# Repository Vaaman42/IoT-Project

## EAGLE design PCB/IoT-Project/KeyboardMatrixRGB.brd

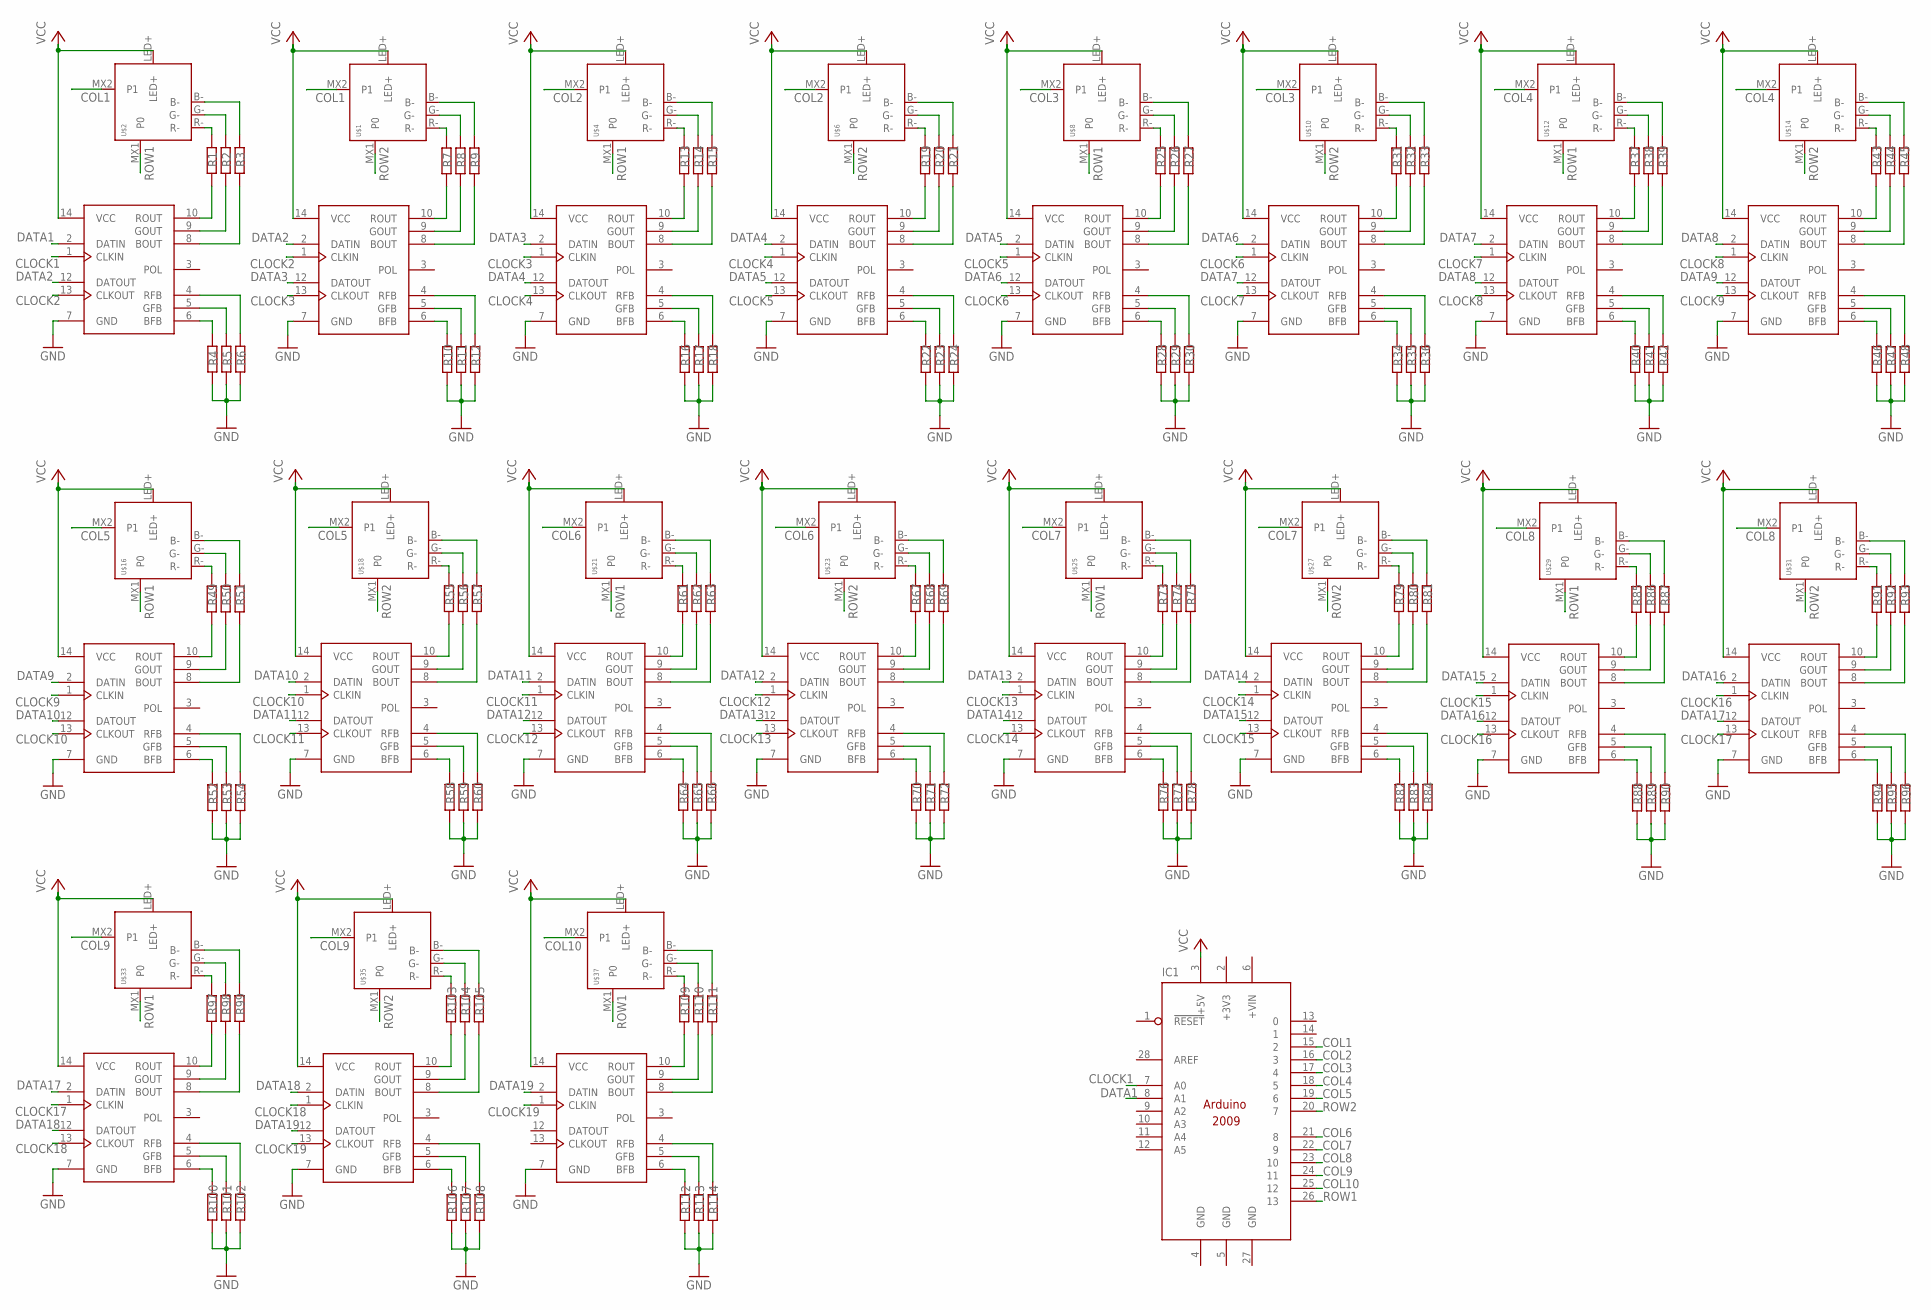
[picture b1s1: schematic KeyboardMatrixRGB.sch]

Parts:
IC1: ARDUINO2009_10; ARDUINO2009
R1, R2, R3, R4, R5, R6, R7, R8, R9, R10, R11, R12, R13, R14, R15, R16, R17, R18, R19, R20, R21, R22, R23, R24, R25, R26, R27, R28, R29, R30, R31, R32, R33, R34, R35, R36, R37, R38, R39, R40, R41, R42, R43, R44, R45, R46, R47, R48, R49, R50, R51, R52, R53, R54, R55, R56, R57, R58, R59, R60, R61, R62, R63, R64, R65, R66, R67, R68, R69, R70, R71, R72, R73, R74, R75, R76, R77, R78, R79, R80, R81, R82, R83, R84, R85, R86, R87, R88, R89, R90, R91, R92, R93, R94, R95, R96, R97, R98, R99, R100, R101, R102, R103, R104, R105, R106, R107, R108, R109, R110, R111, R112, R113, R114: R-EU_0204/5; 0204/5
U$1, U$2, U$4, U$6, U$8, U$10, U$12, U$14, U$16, U$18, U$21, U$23, U$25, U$27, U$29, U$31, U$33, U$35, U$37: KEYSWITCH-RGBLED-MX-1U-RGB; MX-1U-RGB
U$3, U$5, U$7, U$9, U$11, U$13, U$15, U$17, U$19, U$20, U$22, U$24, U$26, U$28, U$30, U$32, U$34, U$36, U$38: WS2801; SOP14

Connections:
+3V3: IC1.2 (+3V3)
CLOCK1: IC1.7 (A0), U$20.1 (CLKIN)
CLOCK2: U$3.1 (CLKIN), U$20.13 (CLKOUT)
CLOCK3: U$3.13 (CLKOUT), U$5.1 (CLKIN)
CLOCK4: U$5.13 (CLKOUT), U$7.1 (CLKIN)
CLOCK5: U$7.13 (CLKOUT), U$9.1 (CLKIN)
CLOCK6: U$9.13 (CLKOUT), U$11.1 (CLKIN)
CLOCK7: U$11.13 (CLKOUT), U$13.1 (CLKIN)
CLOCK8: U$13.13 (CLKOUT), U$15.1 (CLKIN)
CLOCK9: U$15.13 (CLKOUT), U$17.1 (CLKIN)
CLOCK10: U$17.13 (CLKOUT), U$19.1 (CLKIN)
CLOCK11: U$19.13 (CLKOUT), U$22.1 (CLKIN)
CLOCK12: U$22.13 (CLKOUT), U$24.1 (CLKIN)
CLOCK13: U$24.13 (CLKOUT), U$26.1 (CLKIN)
CLOCK14: U$26.13 (CLKOUT), U$28.1 (CLKIN)
CLOCK15: U$28.13 (CLKOUT), U$30.1 (CLKIN)
CLOCK16: U$30.13 (CLKOUT), U$32.1 (CLKIN)
CLOCK17: U$32.13 (CLKOUT), U$34.1 (CLKIN)
CLOCK18: U$34.13 (CLKOUT), U$36.1 (CLKIN)
CLOCK19: U$36.13 (CLKOUT), U$38.1 (CLKIN)
COL1: IC1.15 (2), U$1.MX2 (P1), U$2.MX2 (P1)
COL2: IC1.16 (3), U$4.MX2 (P1), U$6.MX2 (P1)
COL3: IC1.17 (4), U$8.MX2 (P1), U$10.MX2 (P1)
COL4: IC1.18 (5), U$12.MX2 (P1), U$14.MX2 (P1)
COL5: IC1.19 (6), U$16.MX2 (P1), U$18.MX2 (P1)
COL6: IC1.21 (8), U$21.MX2 (P1), U$23.MX2 (P1)
COL7: IC1.22 (9), U$25.MX2 (P1), U$27.MX2 (P1)
COL8: IC1.23 (10), U$29.MX2 (P1), U$31.MX2 (P1)
COL9: IC1.24 (11), U$33.MX2 (P1), U$35.MX2 (P1)
COL10: IC1.25 (12), U$37.MX2 (P1)
DATA1: IC1.8 (A1), U$20.2 (DATIN)
DATA2: U$3.2 (DATIN), U$20.12 (DATOUT)
DATA3: U$3.12 (DATOUT), U$5.2 (DATIN)
DATA4: U$5.12 (DATOUT), U$7.2 (DATIN)
DATA5: U$7.12 (DATOUT), U$9.2 (DATIN)
DATA6: U$9.12 (DATOUT), U$11.2 (DATIN)
DATA7: U$11.12 (DATOUT), U$13.2 (DATIN)
DATA8: U$13.12 (DATOUT), U$15.2 (DATIN)
DATA9: U$15.12 (DATOUT), U$17.2 (DATIN)
DATA10: U$17.12 (DATOUT), U$19.2 (DATIN)
DATA11: U$19.12 (DATOUT), U$22.2 (DATIN)
DATA12: U$22.12 (DATOUT), U$24.2 (DATIN)
DATA13: U$24.12 (DATOUT), U$26.2 (DATIN)
DATA14: U$26.12 (DATOUT), U$28.2 (DATIN)
DATA15: U$28.12 (DATOUT), U$30.2 (DATIN)
DATA16: U$30.12 (DATOUT), U$32.2 (DATIN)
DATA17: U$32.12 (DATOUT), U$34.2 (DATIN)
DATA18: U$34.12 (DATOUT), U$36.2 (DATIN)
DATA19: U$36.12 (DATOUT), U$38.2 (DATIN)
GND: IC1.4 (GND), IC1.5 (GND), IC1.27 (GND), R4.1, R5.1, R6.1, R10.1, R11.1, R12.1, R16.1, R17.1, R18.1, R22.1, R23.1, R24.1, R28.1, R29.1, R30.1, R34.1, R35.1, R36.1, R40.1, R41.1, R42.1, R46.1, R47.1, R48.1, R52.1, R53.1, R54.1, R58.1, R59.1, R60.1, R64.1, R65.1, R66.1, R70.1, R71.1, R72.1, R76.1, R77.1, R78.1, R82.1, R83.1, R84.1, R88.1, R89.1, R90.1, R94.1, R95.1, R96.1, R100.1, R101.1, R102.1, R106.1, R107.1, R108.1, R112.1, R113.1, R114.1, U$3.7 (GND), U$5.7 (GND), U$7.7 (GND), U$9.7 (GND), U$11.7 (GND), U$13.7 (GND), U$15.7 (GND), U$17.7 (GND), U$19.7 (GND), U$20.7 (GND), U$22.7 (GND), U$24.7 (GND), U$26.7 (GND), U$28.7 (GND), U$30.7 (GND), U$32.7 (GND), U$34.7 (GND), U$36.7 (GND), U$38.7 (GND)
unnamed: R1.2, U$2.R-
unnamed: R2.2, U$2.G-
unnamed: R3.2, U$2.B-
unnamed: R1.1, U$20.10 (ROUT)
unnamed: R2.1, U$20.9 (GOUT)
unnamed: R3.1, U$20.8 (BOUT)
unnamed: R4.2, U$20.6 (BFB)
unnamed: R5.2, U$20.5 (GFB)
unnamed: R6.2, U$20.4 (RFB)
unnamed: R49.2, U$16.R-
unnamed: R7.2, U$1.R-
unnamed: R8.2, U$1.G-
unnamed: R9.2, U$1.B-
unnamed: R7.1, U$3.10 (ROUT)
unnamed: R8.1, U$3.9 (GOUT)
unnamed: R9.1, U$3.8 (BOUT)
unnamed: R10.2, U$3.6 (BFB)
unnamed: R11.2, U$3.5 (GFB)
unnamed: R12.2, U$3.4 (RFB)
unnamed: R13.2, U$4.R-
unnamed: R14.2, U$4.G-
unnamed: R15.2, U$4.B-
unnamed: R13.1, U$5.10 (ROUT)
unnamed: R14.1, U$5.9 (GOUT)
unnamed: R15.1, U$5.8 (BOUT)
unnamed: R16.2, U$5.6 (BFB)
unnamed: R17.2, U$5.5 (GFB)
unnamed: R18.2, U$5.4 (RFB)
unnamed: R19.2, U$6.R-
unnamed: R20.2, U$6.G-
unnamed: R21.2, U$6.B-
unnamed: R19.1, U$7.10 (ROUT)
unnamed: R20.1, U$7.9 (GOUT)
unnamed: R21.1, U$7.8 (BOUT)
unnamed: R22.2, U$7.6 (BFB)
unnamed: R23.2, U$7.5 (GFB)
unnamed: R24.2, U$7.4 (RFB)
unnamed: R25.2, U$8.R-
unnamed: R26.2, U$8.G-
unnamed: R27.2, U$8.B-
unnamed: R25.1, U$9.10 (ROUT)
unnamed: R26.1, U$9.9 (GOUT)
unnamed: R27.1, U$9.8 (BOUT)
unnamed: R28.2, U$9.6 (BFB)
unnamed: R29.2, U$9.5 (GFB)
unnamed: R30.2, U$9.4 (RFB)
unnamed: R31.2, U$10.R-
unnamed: R32.2, U$10.G-
unnamed: R33.2, U$10.B-
unnamed: R31.1, U$11.10 (ROUT)
unnamed: R32.1, U$11.9 (GOUT)
unnamed: R33.1, U$11.8 (BOUT)
unnamed: R34.2, U$11.6 (BFB)
unnamed: R35.2, U$11.5 (GFB)
unnamed: R36.2, U$11.4 (RFB)
unnamed: R37.2, U$12.R-
unnamed: R38.2, U$12.G-
unnamed: R39.2, U$12.B-
unnamed: R37.1, U$13.10 (ROUT)
unnamed: R38.1, U$13.9 (GOUT)
unnamed: R39.1, U$13.8 (BOUT)
unnamed: R40.2, U$13.6 (BFB)
unnamed: R41.2, U$13.5 (GFB)
unnamed: R42.2, U$13.4 (RFB)
unnamed: R43.2, U$14.R-
unnamed: R44.2, U$14.G-
unnamed: R45.2, U$14.B-
unnamed: R43.1, U$15.10 (ROUT)
unnamed: R44.1, U$15.9 (GOUT)
unnamed: R45.1, U$15.8 (BOUT)
unnamed: R46.2, U$15.6 (BFB)
unnamed: R47.2, U$15.5 (GFB)
unnamed: R48.2, U$15.4 (RFB)
unnamed: R50.2, U$16.G-
unnamed: R51.2, U$16.B-
unnamed: R49.1, U$17.10 (ROUT)
unnamed: R50.1, U$17.9 (GOUT)
unnamed: R51.1, U$17.8 (BOUT)
unnamed: R52.2, U$17.6 (BFB)
unnamed: R53.2, U$17.5 (GFB)
unnamed: R54.2, U$17.4 (RFB)
unnamed: R97.2, U$33.R-
unnamed: R55.2, U$18.R-
unnamed: R56.2, U$18.G-
unnamed: R57.2, U$18.B-
unnamed: R55.1, U$19.10 (ROUT)
unnamed: R56.1, U$19.9 (GOUT)
unnamed: R57.1, U$19.8 (BOUT)
unnamed: R58.2, U$19.6 (BFB)
unnamed: R59.2, U$19.5 (GFB)
unnamed: R60.2, U$19.4 (RFB)
unnamed: R61.2, U$21.R-
unnamed: R62.2, U$21.G-
unnamed: R63.2, U$21.B-
unnamed: R61.1, U$22.10 (ROUT)
unnamed: R62.1, U$22.9 (GOUT)
unnamed: R63.1, U$22.8 (BOUT)
unnamed: R64.2, U$22.6 (BFB)
unnamed: R65.2, U$22.5 (GFB)
unnamed: R66.2, U$22.4 (RFB)
unnamed: R67.2, U$23.R-
unnamed: R68.2, U$23.G-
unnamed: R69.2, U$23.B-
unnamed: R67.1, U$24.10 (ROUT)
unnamed: R68.1, U$24.9 (GOUT)
unnamed: R69.1, U$24.8 (BOUT)
unnamed: R70.2, U$24.6 (BFB)
unnamed: R71.2, U$24.5 (GFB)
unnamed: R72.2, U$24.4 (RFB)
unnamed: R73.2, U$25.R-
unnamed: R74.2, U$25.G-
unnamed: R75.2, U$25.B-
unnamed: R73.1, U$26.10 (ROUT)
unnamed: R74.1, U$26.9 (GOUT)
unnamed: R75.1, U$26.8 (BOUT)
unnamed: R76.2, U$26.6 (BFB)
unnamed: R77.2, U$26.5 (GFB)
unnamed: R78.2, U$26.4 (RFB)
unnamed: R79.2, U$27.R-
unnamed: R80.2, U$27.G-
unnamed: R81.2, U$27.B-
unnamed: R79.1, U$28.10 (ROUT)
unnamed: R80.1, U$28.9 (GOUT)
unnamed: R81.1, U$28.8 (BOUT)
unnamed: R82.2, U$28.6 (BFB)
unnamed: R83.2, U$28.5 (GFB)
unnamed: R84.2, U$28.4 (RFB)
unnamed: R85.2, U$29.R-
unnamed: R86.2, U$29.G-
unnamed: R87.2, U$29.B-
unnamed: R85.1, U$30.10 (ROUT)
unnamed: R86.1, U$30.9 (GOUT)
unnamed: R87.1, U$30.8 (BOUT)
unnamed: R88.2, U$30.6 (BFB)
unnamed: R89.2, U$30.5 (GFB)
unnamed: R90.2, U$30.4 (RFB)
unnamed: R91.2, U$31.R-
unnamed: R92.2, U$31.G-
unnamed: R93.2, U$31.B-
unnamed: R91.1, U$32.10 (ROUT)
unnamed: R92.1, U$32.9 (GOUT)
unnamed: R93.1, U$32.8 (BOUT)
unnamed: R94.2, U$32.6 (BFB)
unnamed: R95.2, U$32.5 (GFB)
unnamed: R96.2, U$32.4 (RFB)
unnamed: R98.2, U$33.G-
unnamed: R99.2, U$33.B-
unnamed: R97.1, U$34.10 (ROUT)
unnamed: R98.1, U$34.9 (GOUT)
unnamed: R99.1, U$34.8 (BOUT)
unnamed: R100.2, U$34.6 (BFB)
unnamed: R101.2, U$34.5 (GFB)
unnamed: R102.2, U$34.4 (RFB)
unnamed: R103.2, U$35.R-
unnamed: R104.2, U$35.G-
unnamed: R105.2, U$35.B-
unnamed: R103.1, U$36.10 (ROUT)
unnamed: R104.1, U$36.9 (GOUT)
unnamed: R105.1, U$36.8 (BOUT)
unnamed: R106.2, U$36.6 (BFB)
unnamed: R107.2, U$36.5 (GFB)
unnamed: R108.2, U$36.4 (RFB)
unnamed: R109.2, U$37.R-
unnamed: R110.2, U$37.G-
unnamed: R111.2, U$37.B-
unnamed: R109.1, U$38.10 (ROUT)
unnamed: R110.1, U$38.9 (GOUT)
unnamed: R111.1, U$38.8 (BOUT)
unnamed: R112.2, U$38.6 (BFB)
unnamed: R113.2, U$38.5 (GFB)
unnamed: R114.2, U$38.4 (RFB)
ROW1: IC1.26 (13), U$2.MX1 (P0), U$4.MX1 (P0), U$8.MX1 (P0), U$12.MX1 (P0), U$16.MX1 (P0), U$21.MX1 (P0), U$25.MX1 (P0), U$29.MX1 (P0), U$33.MX1 (P0), U$37.MX1 (P0)
ROW2: IC1.20 (7), U$1.MX1 (P0), U$6.MX1 (P0), U$10.MX1 (P0), U$14.MX1 (P0), U$18.MX1 (P0), U$23.MX1 (P0), U$27.MX1 (P0), U$31.MX1 (P0), U$35.MX1 (P0)
VCC: IC1.3 (+5V), U$1.LED+, U$2.LED+, U$3.14 (VCC), U$4.LED+, U$5.14 (VCC), U$6.LED+, U$7.14 (VCC), U$8.LED+, U$9.14 (VCC), U$10.LED+, U$11.14 (VCC), U$12.LED+, U$13.14 (VCC), U$14.LED+, U$15.14 (VCC), U$16.LED+, U$17.14 (VCC), U$18.LED+, U$19.14 (VCC), U$20.14 (VCC), U$21.LED+, U$22.14 (VCC), U$23.LED+, U$24.14 (VCC), U$25.LED+, U$26.14 (VCC), U$27.LED+, U$28.14 (VCC), U$29.LED+, U$30.14 (VCC), U$31.LED+, U$32.14 (VCC), U$33.LED+, U$34.14 (VCC), U$35.LED+, U$36.14 (VCC), U$37.LED+, U$38.14 (VCC)

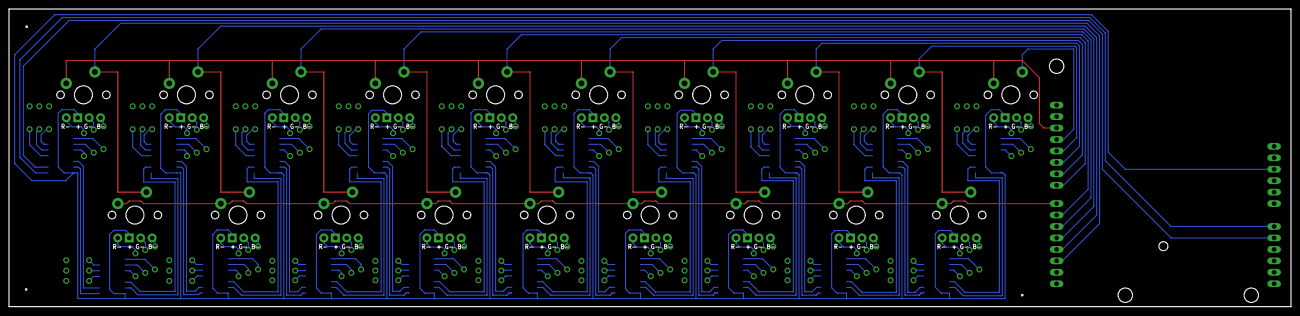
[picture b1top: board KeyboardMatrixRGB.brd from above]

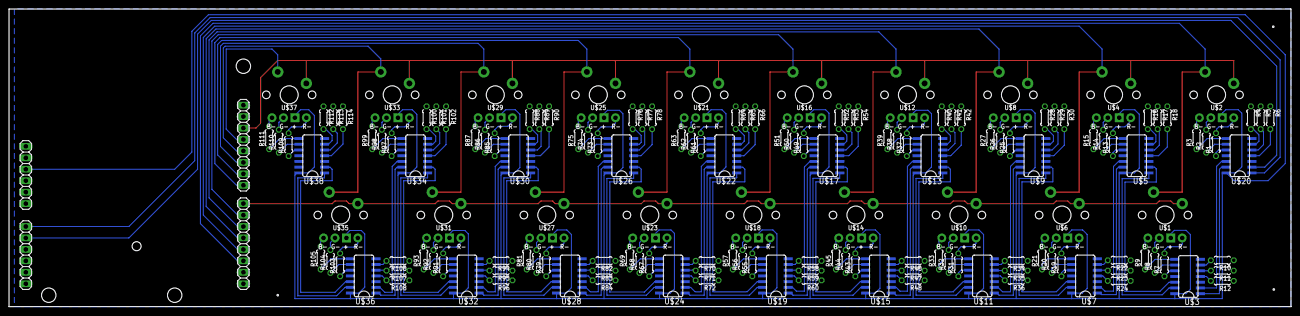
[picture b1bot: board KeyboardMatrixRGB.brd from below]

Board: 2 copper layers, 284.4 x 66.0 mm, 153 parts (134 on the bottom side), 223 nets.

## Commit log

2021-04-21 Migration to this repo
